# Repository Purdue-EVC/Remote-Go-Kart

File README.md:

# Rc Go Kart
The Purdue EVC Club's code for the Rc Go kart.
## Setup
Currently using a red line 775 for the steering motor with a SparkMini as the motor controller.
Then using a Rev Robotics Through Bore Encoder for the steering shaft's positioning.
For the brakes we use a linear actuator with a potentiometer as the position sensor.
For motor control we use a sevcon gen4 size 4 with an unknown decade old brushless dc motor.
There is an stm32 controlling the entire kart.
For the remote controller we use a FlySky ia10b receiver with a FlySky i6X for the transmitter.
## Power
Power for all devices except the main motor is entirely from battery power passed through a 48v-12v/5v dc to dc converter. 
12v is supplied to the front steering, braking and the stm32. 5v is supplied to all other devices on the kart.
For the sevcon we use a keyed ignition start along with 2 estops in series connected to the contactor for the sevcon.
Battery power is supplied directly to the sevcon through the contactor.

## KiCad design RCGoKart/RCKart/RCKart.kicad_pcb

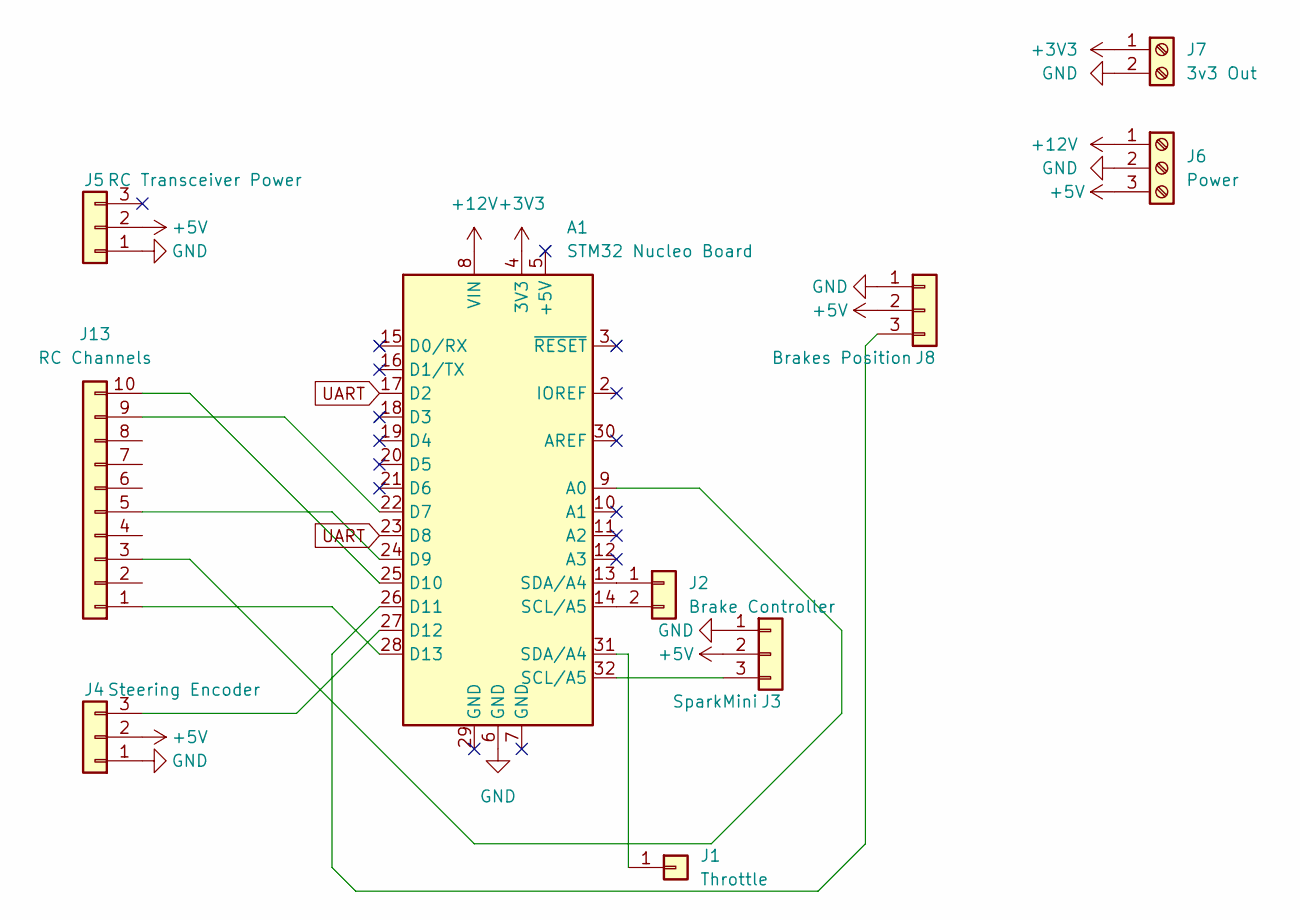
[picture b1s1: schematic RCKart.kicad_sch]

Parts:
A1: STM32 Nucleo Board; Arduino_UNO_R3_Bare
J1: Throttle; PinSocket_1x01_P2.54mm_Vertical
J2: Brake Controller; PinSocket_1x02_P2.54mm_Vertical
J3: SparkMini; PinHeader_1x03_P2.54mm_Vertical
J4: Steering Encoder; PinHeader_1x03_P2.54mm_Vertical
J5: RC Transceiver Power; PinSocket_1x03_P2.54mm_Vertical
J6: Power; TerminalBlock_bornier-3_P5.08mm
J7: 3v3 Out; TerminalBlock_bornier-2_P5.08mm
J8: Brakes Position; PinSocket_1x03_P2.54mm_Vertical
J13: RC Channels; PinSocket_1x10_P2.54mm_Vertical

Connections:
+3V3: A1.4 (3V3), J7.1
+5V: J3.2, J4.2, J5.2, J6.3, J8.2
+12V: A1.8 (VIN), J6.1
GND: A1.6 (GND), J3.1, J4.1, J5.1, J6.2, J7.2, J8.1
unnamed: A1.9 (A0), J13.3
unnamed: A1.22 (D7), J13.9
unnamed: A1.24 (D9), J13.5
unnamed: A1.25 (D10), J13.10
unnamed: A1.26 (D11), J8.3
unnamed: A1.27 (D12), J4.3
unnamed: A1.28 (D13), J13.1
unnamed: A1.31 (SDA/A4), J1.1
unnamed: A1.13 (SDA/A4), J2.1
unnamed: A1.14 (SCL/A5), J2.2
unnamed: A1.32 (SCL/A5), J3.3
UART: A1.17 (D2), A1.23 (D8)

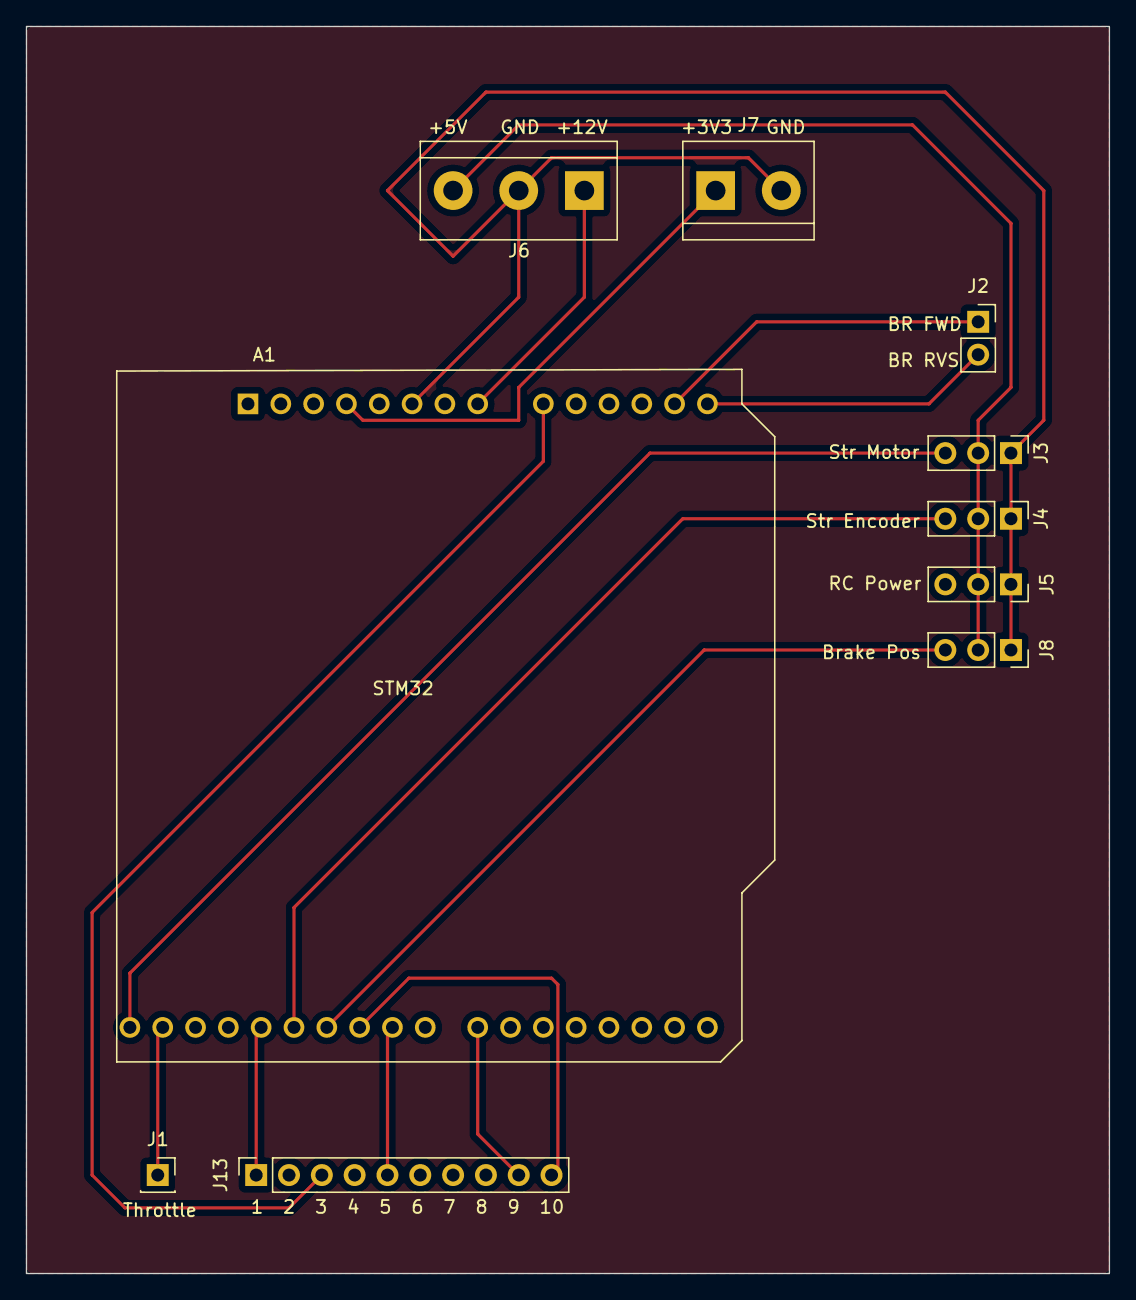
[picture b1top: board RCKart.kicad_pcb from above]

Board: 2 copper layers, 83.8 x 96.5 mm, 10 parts (0 on the bottom side), 16 nets.

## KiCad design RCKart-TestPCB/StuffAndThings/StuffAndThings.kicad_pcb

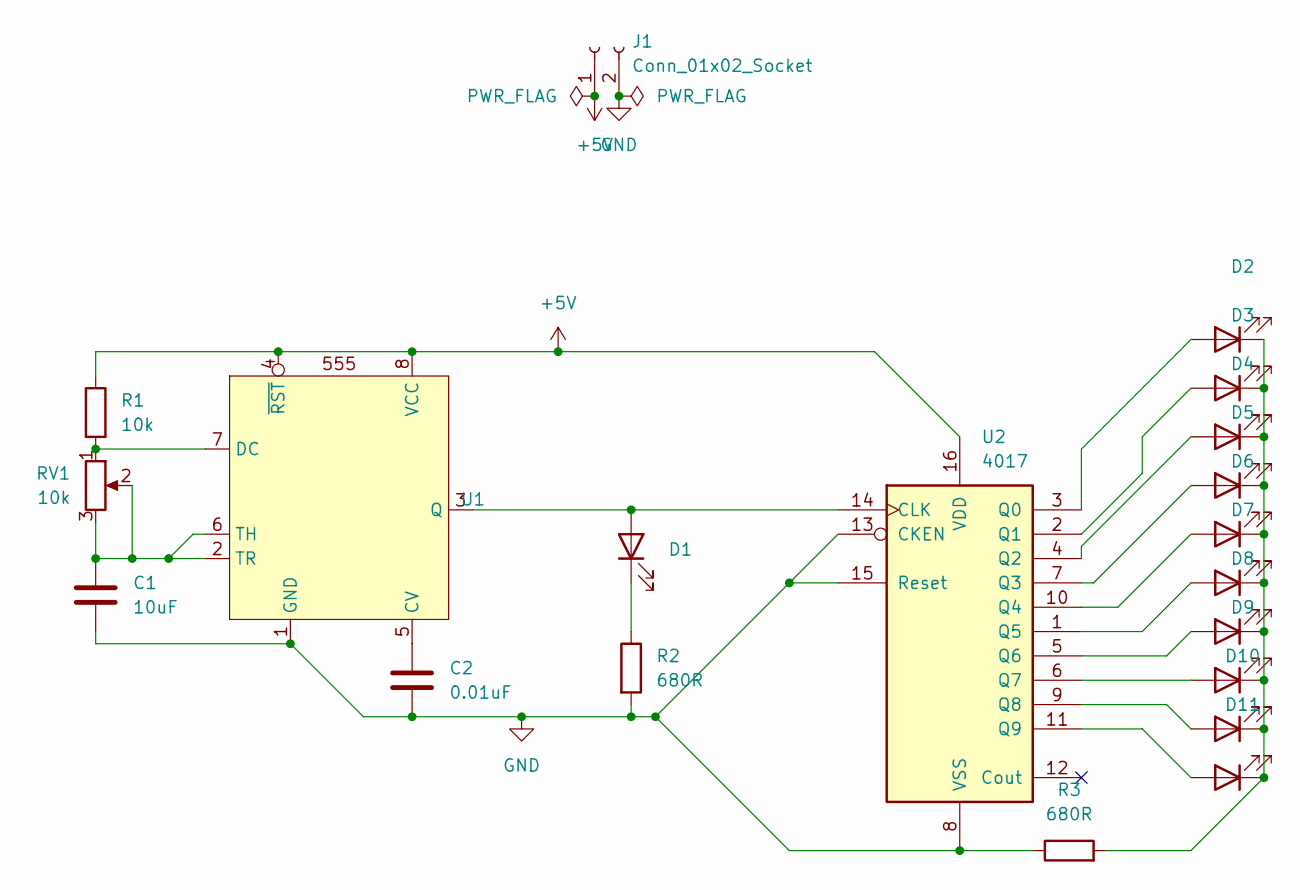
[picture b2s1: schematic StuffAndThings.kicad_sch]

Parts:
C1: 10uF; C_0402_1005Metric
C2: 0.01uF; C_0402_1005Metric
D1, D2, D3, D4, D5, D6, D7, D8, D9, D10, D11: D_0402_1005Metric
J1: Conn_01x02_Socket; PinSocket_1x02_P2.54mm_Vertical
R1: 10k; R_0402_1005Metric
R2: 680R; R_0603_1608Metric
R3: 680R; R_0402_1005Metric
RV1: 10k; Potentiometer_Bourns_3269P_Horizontal
U1: SOIC-8_3.9x4.9mm_P1.27mm
U2: 4017; SOIC-16_3.9x9.9mm_P1.27mm

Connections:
+5V: J1.1, R1.1, U1.4 (~RST), U1.8 (VCC), U2.16 (VDD)
GND: C1.2, C2.2, J1.2, R2.2, R3.1, U1.1 (GND), U2.8 (VSS), U2.13 (CKEN), U2.15 (Reset)
unnamed: D1.2 (A), U1.3 (Q), U2.14 (CLK)
unnamed: D1.1 (K), R2.1
unnamed: D2.2 (A), U2.3 (Q0)
unnamed: D3.2 (A), U2.2 (Q1)
unnamed: D4.2 (A), U2.4 (Q2)
unnamed: D5.2 (A), U2.7 (Q3)
unnamed: D6.2 (A), U2.10 (Q4)
unnamed: D7.2 (A), U2.1 (Q5)
unnamed: D8.2 (A), U2.5 (Q6)
unnamed: D9.2 (A), U2.6 (Q7)
unnamed: D10.2 (A), U2.9 (Q8)
unnamed: D2.1 (K), D3.1 (K), D4.1 (K), D5.1 (K), D6.1 (K), D7.1 (K), D8.1 (K), D9.1 (K), D10.1 (K), D11.1 (K), R3.2
unnamed: D11.2 (A), U2.11 (Q9)
unnamed: C2.1, U1.5 (CV)
unnamed: R1.2, RV1.1, U1.7 (DC)
unnamed: C1.1, RV1.2, RV1.3, U1.2 (TR), U1.6 (TH)

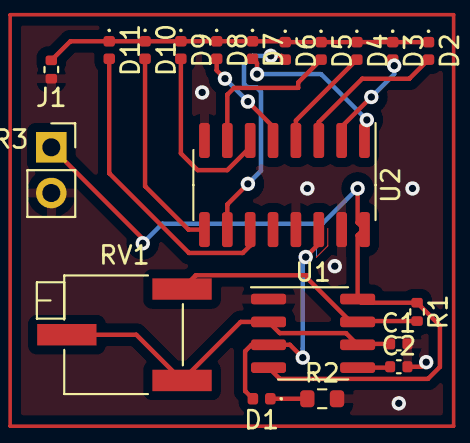
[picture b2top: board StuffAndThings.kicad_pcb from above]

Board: 2 copper layers, 20 parts (0 on the bottom side), 18 nets.

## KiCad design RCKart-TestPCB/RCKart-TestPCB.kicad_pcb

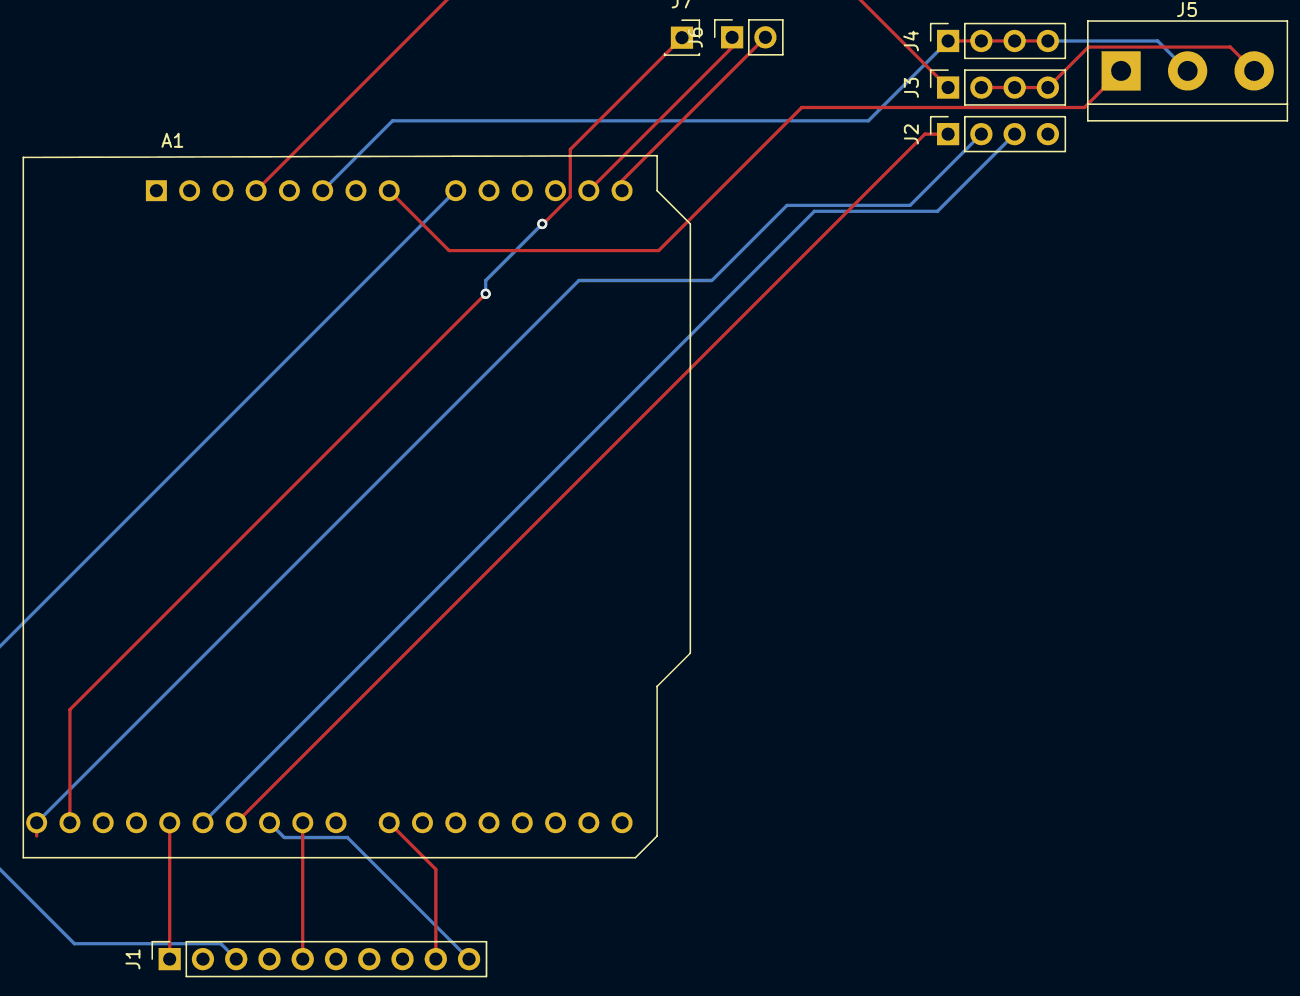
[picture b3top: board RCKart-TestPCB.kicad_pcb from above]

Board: 2 copper layers, 8 parts (0 on the bottom side), 15 nets.

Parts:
A1: STM32 Nucleo Board; Arduino_UNO_R3_Bare
J1: RC Channels; PinSocket_1x10_P2.54mm_Vertical
J2: SIG; PinSocket_1x04_P2.54mm_Vertical
J3: PWR; PinSocket_1x04_P2.54mm_Vertical
J4: GND; PinSocket_1x04_P2.54mm_Vertical
J5: Power; TerminalBlock_bornier-3_P5.08mm
J6: Brake Controller; PinSocket_1x02_P2.54mm_Vertical
J7: Throttle; PinSocket_1x01_P2.54mm_Vertical

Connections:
+3V3: A1.4 (3V3), J3.1
+5V: J3.2, J3.3, J3.4, J5.3
+12V: A1.8 (VIN), J5.1
BP: A1.26 (D11), J2.1
ESTOP: A1.25 (D10), J1.10
GND: A1.6 (GND), J4.1, J4.2, J4.3, J4.4, J5.2
MAX SPD: A1.24 (D9), J1.5
unnamed: A1.13 (SDA/A4), J6.1
unnamed: A1.14 (SCL/A5), J6.2
unnamed: A1.31 (SDA/A4), J7.1
SM: A1.32 (SCL/A5), J2.2
STATE: A1.22 (D7), J1.9
STR ENC: A1.27 (D12), J2.3
STR IN: A1.28 (D13), J1.1
THR IN: A1.9 (A0), J1.3

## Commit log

2023-09-01 Create TalonTestSpeedController.ino
    This code should be able to control the talon srx as if it is a servo with max servo angle as max speed and min angle as off
2023-09-01 Update TalonTestSpeedController.ino
    Fixed bugs and stupid code errors. Added some documentation
2023-09-02 Updated Code
2023-09-02 updated ki
2023-09-02 Create jsTestDebug.js
    Used to test pid programming
2023-09-10 Implement exponential filter
2023-09-10 Switch exponential filter to use library
2023-09-11 WIP Sparkmini controller class
2023-09-18 Uploaded Current STM32 Code
2023-09-18 fixed simple code mismatches
2023-09-18 built code
2023-09-18 Added ConvertPWMInToOut
    converts the pwm in from the rc stick to pwm out for the steering motor
2023-09-18 Updated gitignore
2023-09-18 Uploaded Current Code
2023-09-18 Fixed Uart
2023-09-18 Updated TIM to correct channels
2023-09-19 Added debug code and statemanagement
2023-09-26 Added e-stop conditions
2023-09-26 wip pid and motor control functions
2023-09-29 Finished code ready to debug
2023-10-03 WIP Code
2023-10-03 WIP Schematics
2023-10-03 Fixed % error and attempted fix for UART
    Uart switched to huart2, rawSteeringToAngle now has .01 accuracy and is a float
2023-10-04 Added DAC
2023-10-04 Added DAC, New PID, Fixed Motor Control
    DAC is used to control the motor as it is an analog not a pwm signal. New PID loop has been implemented and read to test, it removes the max angle of the motor by using the P the proper way and limit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
2023-10-05 Working Code Uploaded, PID testing needed
    PID is last thing to test. Motor needs to be debugged but it seems to not be a mcu error.
2023-10-09 Added working code, Need breaks still
2023-10-09 Brakes Implemented
2023-10-24 WIP PCB
2023-10-25 Added Test PCB Wiring
2023-10-26 Test PCB work
2024-02-20 Added Braking, reimplemented all working code for testing
    Braking currently works on pin a4 and a3. Currently steering is ready as well, however gearbox issues are still a wip for the steering motor, after fixes slop may decrease. Driving has not changed si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
    Todo:
    Implement and fix estop relay
    Setup failsafe on controller for kart
    Finish mount for the batteries
    Fix and remount steering motor
2024-02-29 Updated Driving Motor Code
    Code is ready to test on rc kart
